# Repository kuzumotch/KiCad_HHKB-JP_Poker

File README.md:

# KiCad_HHKB-JP_Poker

## Summary
GH60互換疑似JISキーボードPCB  
GH60-compatible JIS-like hotswap keyboard PCB

<!--     -->

## Features  
- MITライセンスのもとでソース公開 / Open-source under the MIT license  
- Kailh製ソケットで全キーホットスワップ可能、はんだ付け無しで組み立て可能 / Fully hotswap  
- GH60対応の60％ケースで使用可能 / Compatible with GH60 standard cases  
- 一般的なキーサイズのみの日本語入力配列なので、GMKやePBTなどの標準キーキャップセットを使用可能 / Features a JIS-like key layout using standard keycap sizes   

[配列データ / Layout data](hhttp://www.keyboard-layout-editor.com/#/gists/5ac90f0792192c119a41c317cfdb1084)

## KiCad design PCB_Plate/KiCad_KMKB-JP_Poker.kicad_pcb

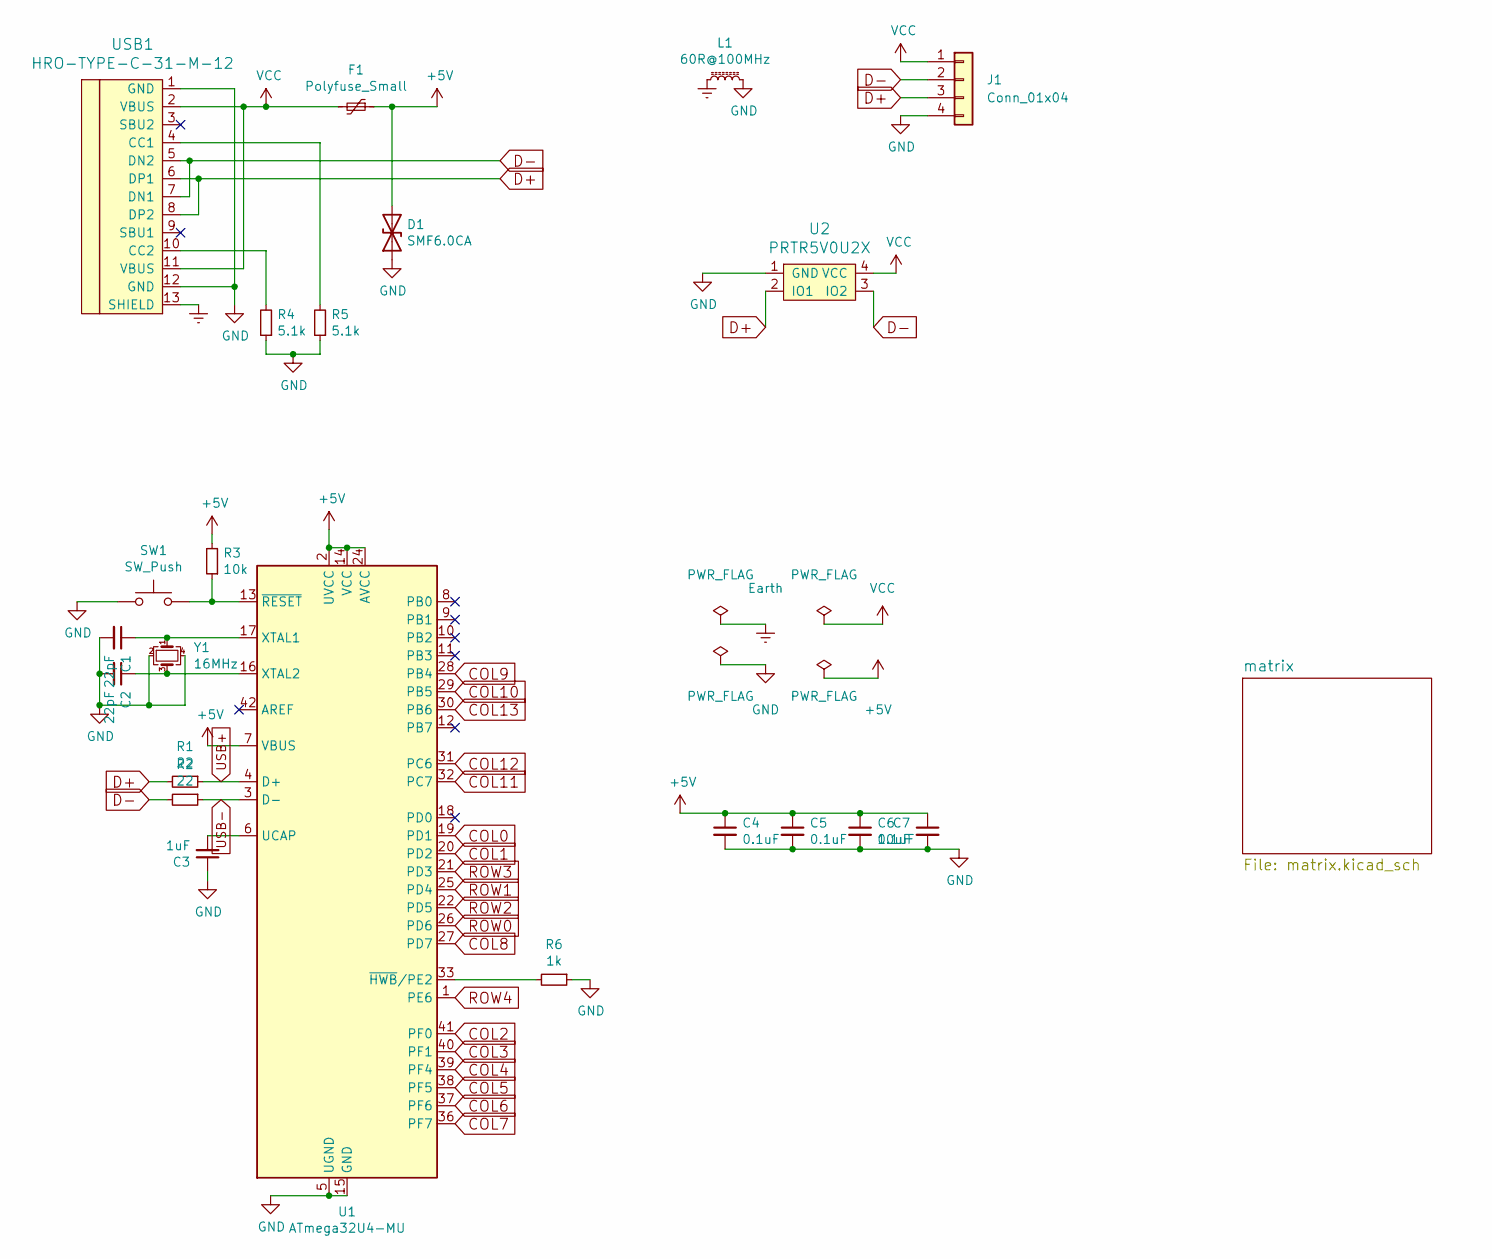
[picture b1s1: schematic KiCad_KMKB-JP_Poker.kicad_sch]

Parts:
C1, C2: 22pF; C_0603_1608Metric
C3: 1uF; C_0603_1608Metric
C4, C5, C6: 0.1uF; C_0603_1608Metric
C7: 10uF; C_0603_1608Metric
D1: SMF6.0CA; D_SOD-123
F1: Polyfuse_Small; Fuse_1206_3216Metric
J1: Conn_01x04; PinHeader_1x04_P2.54mm_Vertical
L1: 60R@100MHz; L_1206_3216Metric
R1, R2: 22; R_0603_1608Metric
R3: 10k; R_0603_1608Metric
R4, R5: 5.1k; R_0603_1608Metric
R6: 1k; R_0603_1608Metric
SW1: SW_Push; SW_SPST_TL3342
U1: ATmega32U4-MU; QFN-44-1EP_7x7mm_P0.5mm_EP5.2x5.2mm
U2: PRTR5V0U2X; SOT143B
USB1: HRO-TYPE-C-31-M-12; HRO-TYPE-C-31-M-12-Assembly
Y1: 16MHz; Crystal_SMD_3225-4Pin_3.2x2.5mm

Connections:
+5V: C4.1, C5.1, C6.1, C7.1, D1.2 (A2), F1.1, R3.2, U1.2 (UVCC), U1.7 (VBUS), U1.14 (VCC), U1.24 (AVCC), U1.34 (VCC), U1.44 (AVCC)
COL0: U1.19 (PD1); also elsewhere on the board
COL1: U1.20 (PD2); also elsewhere on the board
COL2: U1.41 (PF0); also elsewhere on the board
COL3: U1.40 (PF1); also elsewhere on the board
COL4: U1.39 (PF4); also elsewhere on the board
COL5: U1.38 (PF5); also elsewhere on the board
COL6: U1.37 (PF6); also elsewhere on the board
COL7: U1.36 (PF7); also elsewhere on the board
COL8: U1.27 (PD7); also elsewhere on the board
COL9: U1.28 (PB4); also elsewhere on the board
COL10: U1.29 (PB5); also elsewhere on the board
COL11: U1.32 (PC7); also elsewhere on the board
COL12: U1.31 (PC6); also elsewhere on the board
COL13: U1.30 (PB6); also elsewhere on the board
D+: J1.3, R1.2, U2.2 (IO1), USB1.6 (DP1), USB1.8 (DP2)
D-: J1.2, R2.2, U2.3 (IO2), USB1.5 (DN2), USB1.7 (DN1)
Earth: L1.1, USB1.13 (SHIELD)
GND: C1.2, C2.2, C3.1, C4.2, C5.2, C6.2, C7.2, D1.1 (A1), J1.4, L1.2, R4.1, R5.1, R6.1, SW1.1, U1.5 (UGND), U1.15 (GND), U1.23 (GND), U1.35 (GND), U1.43 (GND), U1.45 (GND), U2.1 (GND), USB1.1 (GND), USB1.12 (GND), Y1.2, Y1.4
unnamed: C1.1, U1.17 (XTAL1), Y1.1
unnamed: C2.1, U1.16 (XTAL2), Y1.3
unnamed: C3.2, U1.6 (UCAP)
unnamed: R3.1, SW1.2, U1.13 (~RESET)
unnamed: R4.2, USB1.10 (CC2)
unnamed: R5.2, USB1.4 (CC1)
unnamed: R6.2, U1.33 (~HWB/PE2)
ROW0: U1.26 (PD6); also elsewhere on the board
ROW1: U1.25 (PD4); also elsewhere on the board
ROW2: U1.22 (PD5); also elsewhere on the board
ROW3: U1.21 (PD3); also elsewhere on the board
ROW4: U1.1 (PE6); also elsewhere on the board
USB+: R1.1, U1.4 (D+)
USB-: R2.1, U1.3 (D-)
VCC: F1.2, J1.1, U2.4 (VCC), USB1.2 (VBUS), USB1.11 (VBUS)

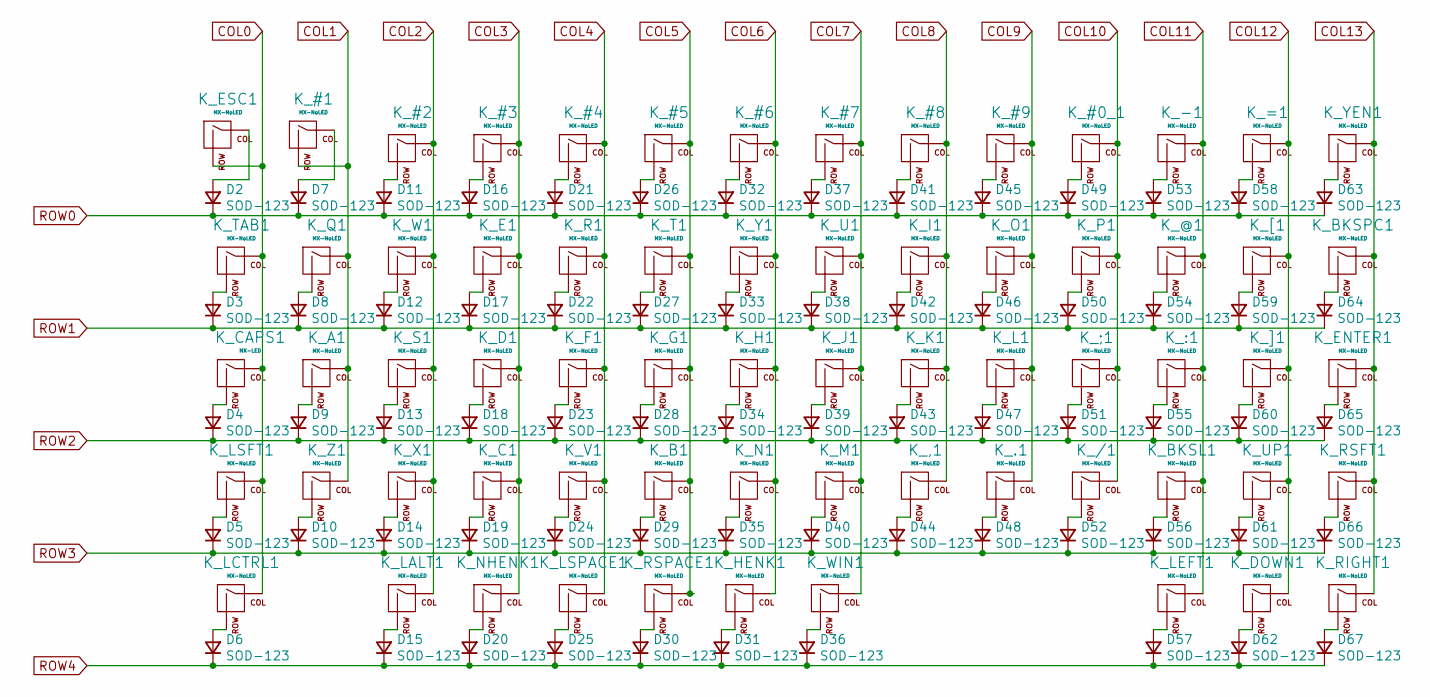
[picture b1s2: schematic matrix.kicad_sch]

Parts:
D2, D3, D4, D5, D6, D7, D8, D9, D10, D11, D12, D13, D14, D15, D16, D17, D18, D19, D20, D21, D22, D23, D24, D25, D26, D27, D28, D29, D30, D31, D32, D33, D34, D35, D36, D37, D38, D39, D40, D41, D42, D43, D44, D45, D46, D47, D48, D49, D50, D51, D52, D53, D54, D55, D56, D57, D58, D59, D60, D61, D62, D63, D64, D65, D66, D67: SOD-123; D_SOD-123
K_#0_1, K_#1, K_#2, K_#3, K_#4, K_#5, K_#6, K_#7, K_#8, K_#9: MX-NoLED; MXOnly-1U-Hotswap
K_,1: MX-NoLED; MXOnly-1U-Hotswap
K_-1: MX-NoLED; MXOnly-1U-Hotswap
K_.1: MX-NoLED; MXOnly-1U-Hotswap
K_/1: MX-NoLED; MXOnly-1U-Hotswap
K_:1: MX-NoLED; MXOnly-1U-Hotswap
K_;1: MX-NoLED; MXOnly-1U-Hotswap
K_=1: MX-NoLED; MXOnly-1U-Hotswap
K_@1: MX-NoLED; MXOnly-1U-Hotswap
K_A1: MX-NoLED; MXOnly-1U-Hotswap
K_B1: MX-NoLED; MXOnly-1U-Hotswap
K_BKSL1: MX-NoLED; MXOnly-1U-Hotswap
K_BKSPC1: MX-NoLED; MXOnly-1U-Hotswap
K_C1: MX-NoLED; MXOnly-1U-Hotswap
K_CAPS1: MX-LED; MXOnly-1.75U-Hotswap
K_D1: MX-NoLED; MXOnly-1U-Hotswap
K_DOWN1: MX-NoLED; MXOnly-1U-Hotswap
K_E1: MX-NoLED; MXOnly-1U-Hotswap
K_ENTER1: MX-NoLED; MXOnly-ISO-ROTATED-Hotswap
K_ESC1: MX-NoLED; MXOnly-1U-Hotswap
K_F1: MX-NoLED; MXOnly-1U-Hotswap
K_G1: MX-NoLED; MXOnly-1U-Hotswap
K_H1: MX-NoLED; MXOnly-1U-Hotswap
K_HENK1: MX-NoLED; MXOnly-1U-Hotswap
K_I1: MX-NoLED; MXOnly-1U-Hotswap
K_J1: MX-NoLED; MXOnly-1U-Hotswap
K_K1: MX-NoLED; MXOnly-1U-Hotswap
K_L1: MX-NoLED; MXOnly-1U-Hotswap
K_LALT1: MX-NoLED; MXOnly-1U-Hotswap
K_LCTRL1: MX-NoLED; MXOnly-1U-Hotswap
K_LEFT1: MX-NoLED; MXOnly-1U-Hotswap
K_LSFT1: MX-NoLED; MXOnly-2U-Hotswap
K_LSPACE1: MX-NoLED; MXOnly-1.25U-Hotswap
K_M1: MX-NoLED; MXOnly-1U-Hotswap
K_N1: MX-NoLED; MXOnly-1U-Hotswap
K_NHENK1: MX-NoLED; MXOnly-1U-Hotswap
K_O1: MX-NoLED; MXOnly-1U-Hotswap
K_P1: MX-NoLED; MXOnly-1U-Hotswap
K_Q1: MX-NoLED; MXOnly-1U-Hotswap
K_R1: MX-NoLED; MXOnly-1U-Hotswap
K_RIGHT1: MX-NoLED; MXOnly-1U-Hotswap
K_RSFT1: MX-NoLED; MXOnly-1U-Hotswap
K_RSPACE1: MX-NoLED; MXOnly-1.25U-Hotswap
K_S1: MX-NoLED; MXOnly-1U-Hotswap
K_T1: MX-NoLED; MXOnly-1U-Hotswap
K_TAB1: MX-NoLED; MXOnly-1.5U-Hotswap
K_U1: MX-NoLED; MXOnly-1U-Hotswap
K_UP1: MX-NoLED; MXOnly-1U-Hotswap
K_V1: MX-NoLED; MXOnly-1U-Hotswap
K_W1: MX-NoLED; MXOnly-1U-Hotswap
K_WIN1: MX-NoLED; MXOnly-1U-Hotswap
K_X1: MX-NoLED; MXOnly-1U-Hotswap
K_Y1: MX-NoLED; MXOnly-1U-Hotswap
K_YEN1: MX-NoLED; MXOnly-1U-Hotswap
K_Z1: MX-NoLED; MXOnly-1U-Hotswap
K_[1: MX-NoLED; MXOnly-1U-Hotswap
K_]1: MX-NoLED; MXOnly-1U-Hotswap

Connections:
COL0: K_CAPS1.1 (COL), K_ESC1.2 (ROW), K_LCTRL1.1 (COL), K_LSFT1.1 (COL), K_TAB1.1 (COL); also elsewhere on the board
COL1: K_#1.2 (ROW), K_A1.1 (COL), K_Q1.1 (COL), K_Z1.1 (COL); also elsewhere on the board
COL2: K_#2.1 (COL), K_LALT1.1 (COL), K_S1.1 (COL), K_W1.1 (COL), K_X1.1 (COL); also elsewhere on the board
COL3: K_#3.1 (COL), K_C1.1 (COL), K_D1.1 (COL), K_E1.1 (COL), K_NHENK1.1 (COL); also elsewhere on the board
COL4: K_#4.1 (COL), K_F1.1 (COL), K_LSPACE1.1 (COL), K_R1.1 (COL), K_V1.1 (COL); also elsewhere on the board
COL5: K_#5.1 (COL), K_B1.1 (COL), K_G1.1 (COL), K_RSPACE1.1 (COL), K_T1.1 (COL); also elsewhere on the board
COL6: K_#6.1 (COL), K_H1.1 (COL), K_HENK1.1 (COL), K_N1.1 (COL), K_Y1.1 (COL); also elsewhere on the board
COL7: K_#7.1 (COL), K_J1.1 (COL), K_M1.1 (COL), K_U1.1 (COL), K_WIN1.1 (COL); also elsewhere on the board
COL8: K_#8.1 (COL), K_,1.1 (COL), K_I1.1 (COL), K_K1.1 (COL); also elsewhere on the board
COL9: K_#9.1 (COL), K_.1.1 (COL), K_L1.1 (COL), K_O1.1 (COL); also elsewhere on the board
COL10: K_#0_1.1 (COL), K_/1.1 (COL), K_;1.1 (COL), K_P1.1 (COL); also elsewhere on the board
COL11: K_-1.1 (COL), K_:1.1 (COL), K_@1.1 (COL), K_BKSL1.1 (COL), K_LEFT1.1 (COL); also elsewhere on the board
COL12: K_=1.1 (COL), K_DOWN1.1 (COL), K_UP1.1 (COL), K_[1.1 (COL), K_]1.1 (COL); also elsewhere on the board
COL13: K_BKSPC1.1 (COL), K_ENTER1.1 (COL), K_RIGHT1.1 (COL), K_RSFT1.1 (COL), K_YEN1.1 (COL); also elsewhere on the board
unnamed: D2.2 (A), K_ESC1.1 (COL)
unnamed: D3.2 (A), K_TAB1.2 (ROW)
unnamed: D4.2 (A), K_CAPS1.2 (ROW)
unnamed: D5.2 (A), K_LSFT1.2 (ROW)
unnamed: D6.2 (A), K_LCTRL1.2 (ROW)
unnamed: D7.2 (A), K_#1.1 (COL)
unnamed: D8.2 (A), K_Q1.2 (ROW)
unnamed: D9.2 (A), K_A1.2 (ROW)
unnamed: D10.2 (A), K_Z1.2 (ROW)
unnamed: D11.2 (A), K_#2.2 (ROW)
unnamed: D12.2 (A), K_W1.2 (ROW)
unnamed: D13.2 (A), K_S1.2 (ROW)
unnamed: D14.2 (A), K_X1.2 (ROW)
unnamed: D15.2 (A), K_LALT1.2 (ROW)
unnamed: D16.2 (A), K_#3.2 (ROW)
unnamed: D17.2 (A), K_E1.2 (ROW)
unnamed: D18.2 (A), K_D1.2 (ROW)
unnamed: D19.2 (A), K_C1.2 (ROW)
unnamed: D20.2 (A), K_NHENK1.2 (ROW)
unnamed: D21.2 (A), K_#4.2 (ROW)
unnamed: D22.2 (A), K_R1.2 (ROW)
unnamed: D23.2 (A), K_F1.2 (ROW)
unnamed: D24.2 (A), K_V1.2 (ROW)
unnamed: D25.2 (A), K_LSPACE1.2 (ROW)
unnamed: D26.2 (A), K_#5.2 (ROW)
unnamed: D27.2 (A), K_T1.2 (ROW)
unnamed: D28.2 (A), K_G1.2 (ROW)
unnamed: D29.2 (A), K_B1.2 (ROW)
unnamed: D30.2 (A), K_RSPACE1.2 (ROW)
unnamed: D31.2 (A), K_HENK1.2 (ROW)
unnamed: D32.2 (A), K_#6.2 (ROW)
unnamed: D33.2 (A), K_Y1.2 (ROW)
unnamed: D34.2 (A), K_H1.2 (ROW)
unnamed: D35.2 (A), K_N1.2 (ROW)
unnamed: D36.2 (A), K_WIN1.2 (ROW)
unnamed: D37.2 (A), K_#7.2 (ROW)
unnamed: D38.2 (A), K_U1.2 (ROW)
unnamed: D39.2 (A), K_J1.2 (ROW)
unnamed: D40.2 (A), K_M1.2 (ROW)
unnamed: D41.2 (A), K_#8.2 (ROW)
unnamed: D42.2 (A), K_I1.2 (ROW)
unnamed: D43.2 (A), K_K1.2 (ROW)
unnamed: D44.2 (A), K_,1.2 (ROW)
unnamed: D45.2 (A), K_#9.2 (ROW)
unnamed: D46.2 (A), K_O1.2 (ROW)
unnamed: D47.2 (A), K_L1.2 (ROW)
unnamed: D48.2 (A), K_.1.2 (ROW)
unnamed: D49.2 (A), K_#0_1.2 (ROW)
unnamed: D50.2 (A), K_P1.2 (ROW)
unnamed: D51.2 (A), K_;1.2 (ROW)
unnamed: D52.2 (A), K_/1.2 (ROW)
unnamed: D53.2 (A), K_-1.2 (ROW)
unnamed: D54.2 (A), K_@1.2 (ROW)
unnamed: D55.2 (A), K_:1.2 (ROW)
unnamed: D56.2 (A), K_BKSL1.2 (ROW)
unnamed: D57.2 (A), K_LEFT1.2 (ROW)
unnamed: D58.2 (A), K_=1.2 (ROW)
unnamed: D59.2 (A), K_[1.2 (ROW)
unnamed: D60.2 (A), K_]1.2 (ROW)
unnamed: D61.2 (A), K_UP1.2 (ROW)
unnamed: D62.2 (A), K_DOWN1.2 (ROW)
unnamed: D63.2 (A), K_YEN1.2 (ROW)
unnamed: D64.2 (A), K_BKSPC1.2 (ROW)
unnamed: D65.2 (A), K_ENTER1.2 (ROW)
unnamed: D66.2 (A), K_RSFT1.2 (ROW)
unnamed: D67.2 (A), K_RIGHT1.2 (ROW)
ROW0: D2.1 (K), D7.1 (K), D11.1 (K), D16.1 (K), D21.1 (K), D26.1 (K), D32.1 (K), D37.1 (K), D41.1 (K), D45.1 (K), D49.1 (K), D53.1 (K), D58.1 (K), D63.1 (K); also elsewhere on the board
ROW1: D3.1 (K), D8.1 (K), D12.1 (K), D17.1 (K), D22.1 (K), D27.1 (K), D33.1 (K), D38.1 (K), D42.1 (K), D46.1 (K), D50.1 (K), D54.1 (K), D59.1 (K), D64.1 (K); also elsewhere on the board
ROW2: D4.1 (K), D9.1 (K), D13.1 (K), D18.1 (K), D23.1 (K), D28.1 (K), D34.1 (K), D39.1 (K), D43.1 (K), D47.1 (K), D51.1 (K), D55.1 (K), D60.1 (K), D65.1 (K); also elsewhere on the board
ROW3: D5.1 (K), D10.1 (K), D14.1 (K), D19.1 (K), D24.1 (K), D29.1 (K), D35.1 (K), D40.1 (K), D44.1 (K), D48.1 (K), D52.1 (K), D56.1 (K), D61.1 (K), D66.1 (K); also elsewhere on the board
ROW4: D6.1 (K), D15.1 (K), D20.1 (K), D25.1 (K), D30.1 (K), D31.1 (K), D36.1 (K), D57.1 (K), D62.1 (K), D67.1 (K); also elsewhere on the board

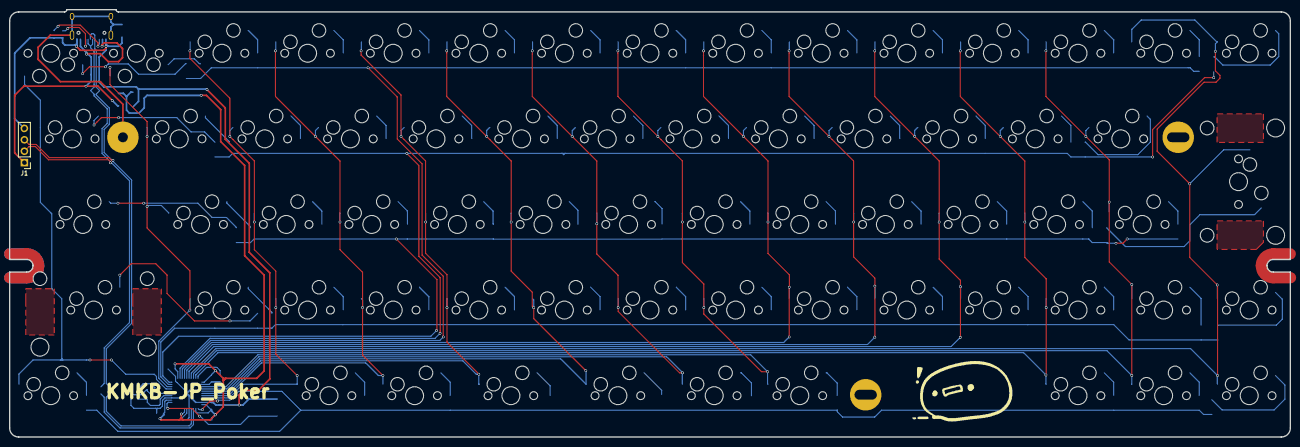
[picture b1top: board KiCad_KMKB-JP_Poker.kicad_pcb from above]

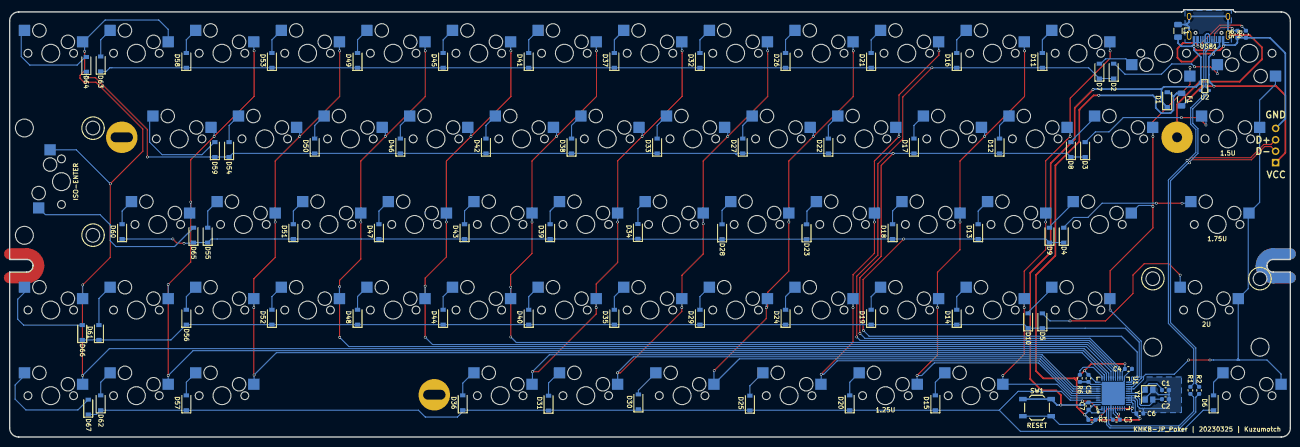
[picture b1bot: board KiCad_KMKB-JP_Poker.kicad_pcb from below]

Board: 2 copper layers, 285.0 x 95.1 mm, 154 parts (87 on the bottom side), 100 nets.

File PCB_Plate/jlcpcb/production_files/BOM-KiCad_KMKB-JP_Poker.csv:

Comment,Designator,Footprint,LCSC
SMF6.0CA,D1,D_SOD-123,C123791
16MHz,Y1,Crystal_SMD_3225-4Pin_3.2x2.5mm,C13738
0.1uF,"C4,C5,C6",C_0603_1608Metric,C14663
1uF,C3,C_0603_1608Metric,C15849
22pF,"C1,C2",C_0603_1608Metric,C1653
HRO-TYPE-C-31-M-12,USB1,HRO-TYPE-C-31-M-12-Assembly,C165948
10uF,C7,C_0603_1608Metric,C19702
1k,R6,R_0603_1608Metric,C21190
5.1k,"R4,R5",R_0603_1608Metric,C23186
22,"R1,R2",R_0603_1608Metric,C23345
10k,R3,R_0603_1608Metric,C25804
SW_Push,SW1,SW_SPST_TL3342,C318884
60R@100MHz,L1,L_1206_3216Metric,C33600
ATmega32U4-MU,U1,QFN-44-1EP_7x7mm_P0.5mm_EP5.2x5.2mm,C45874
MX-NoLED,"K_A1,K_B1,K_BKSL1,K_BKSPC1,K_C1,K_CAPS1,K_D1,K_DOWN1,K_E1,K_ENTER1,K_ESC1,K_F1,K_G1,K_H1,K_HENK1,K_I1,K_J1,K_K1,K_L1,K_LALT1,K_LCTRL1,K_LEFT1,K_LSFT1,K_LSPACE1,K_M1,K_N1,K_NHENK1,K_O1,K_P1,K_Q1,K_R1,K_RIGHT1,K_RSFT1,K_RSPACE1,K_S1,K_T1,K_TAB1,K_U1,K_UP1,K_V1,K_W1,K_WIN1,K_X1,K_Y1,K_YEN1,K_Z1",MXOnly-1U-Hotswap,C5156480
Polyfuse_Small,F1,Fuse_1206_3216Metric,C70082
PRTR5V0U2X,U2,SOT143B,C78442
SOD-123,"D10,D11,D12,D13,D14,D15,D16,D17,D18,D19,D2,D20,D21,D22,D23,D24,D25,D26,D27,D28,D29,D3,D30,D31,D32,D33,D34,D35,D36,D37,D38,D39,D4,D40,D41,D42,D43,D44,D45,D46,D47,D48,D49,D5,D50,D51,D52,D53,D54,D55,D56,D57,D58,D59,D6,D60,D61,D62,D63,D64,D65,D66,D67,D7,D8,D9",D_SOD-123,C81598

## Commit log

2023-03-21 initialize for KiCad_HHKB-JP_Poker
2023-03-21 Edit LICENSE FILE
2023-03-21 edit symbol it does not exist in 6.0
2023-03-21 Edit Key Matrix
2023-03-21 add Layout File
2023-03-21 edit README.md file (add layout)
2023-03-21 edit footprint of Keyswitches.
2023-03-21 Edit sch, execute ERC, and fix warnings
2023-03-21 Modify Symbol Name
2023-03-21 回路図に反映
2023-03-21 Create New Locallib (DZ60 Outline, but does not have center hole)
2023-03-21 Save Point 1 (Start PCB Editing)
2023-03-21 Save Point 2 (Remove ai03's logos)
2023-03-21 Save Point 3 (Remove F:Cu on R4)
2023-03-21 Save Point4 (Move MCU)
2023-03-21 Save Point 5 (Remove B:Cu on R4)
2023-03-21 Correct Symbol Names (bkspとかの辺)
2023-03-21 B.Cuの消し残しを削除
2023-03-21 RIGHT の Footprint を 1.25 -> 1U に変更
2023-03-21 SAVE POINT
2023-03-21 KeySwitchを置き換えていく
2023-03-21 R4(zxc列)のキースイッチ配置完了
2023-03-21 R4(space列)の配置完了
2023-03-21 Diodeの配置完了
2023-03-21 MCUの配置完了
2023-03-21 SAVE POINT (ここから配線タイム)
2023-03-22 配線途中1
2023-03-24 colの配線完了
2023-03-24 時間的にいったんここまで
2023-03-25 回路図エディターで COL14を追加
2023-03-25 回路図エディターで COL14削除、結局 JP60から、 ]と backspace の位置だけ変更した
2023-03-25 縦（Col）の配線完了
2023-03-25 key switch 間の配線は完了。これから、Key Switch と MCUを使う
2023-03-25 配線完了（検算はこれから）
2023-03-25 検算完了！完成！
2023-03-25 ねじ穴のMask削除&中央下をねじ穴に
2023-03-25 電源配線を穴を避けて配線しなおした
2023-03-25 DRCチェック（未配線を修正）
2023-03-25 微修正完了
2023-03-25 HHKB -> HMKB へ変更。 / ロゴの位置を変更
2023-03-25 ファイル名変更 HHKB -> KMKB & フォルダ構成変更
2023-03-25 フォルダ構造を大胆に変更（バグったとしたらココ）
2023-03-29 ドーターボード用の配線穴を設置
2023-03-29 ドーターボード用の配線穴の位置を微修正
2023-03-31 シルクを修正
2023-03-31 JCLPCBに発注しました
2023-04-02 remove ゴミファイル
2023-04-02 SWソケットを BOMとPOSファイルから削除
2023-04-02 Initialize Power SwitchPlate Folder
2023-04-02 サリチル酸さんのライブラリを追加（TopPlateに）
2023-04-02 SAVE POINT2
